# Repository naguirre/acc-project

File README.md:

# acc-project
Another Cubetto Clone project : this repository contains all assets (mechanical, sw and hardware) for ACC project

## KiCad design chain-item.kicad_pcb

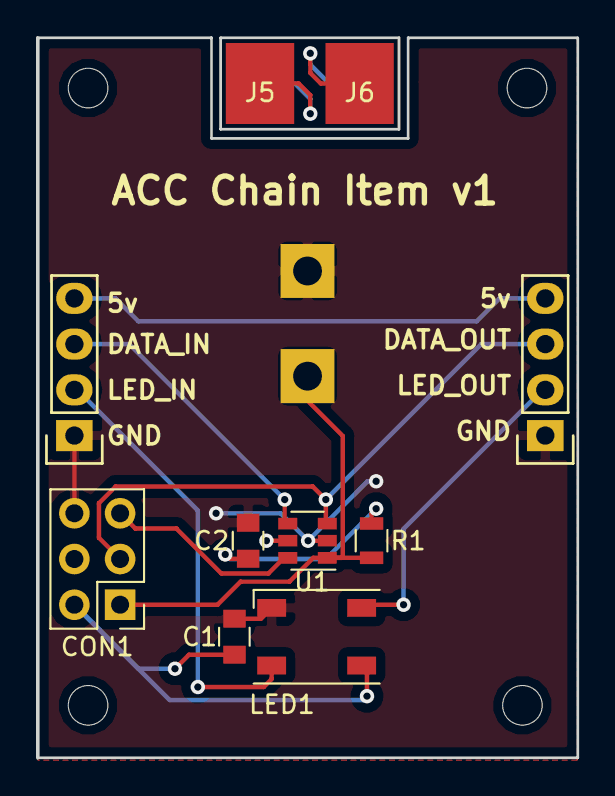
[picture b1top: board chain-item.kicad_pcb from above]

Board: 2 copper layers, 30.0 x 40.0 mm, 17 parts (1 on the bottom side), 11 nets.

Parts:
C1, C2: C_Small; C_0805
CON1: AVR-ISP-6; Pin_Header_Straight_2x03_Pitch2.54mm
J1, J4: Conn_01x04; Pin_Header_Straight_1x04
J2: R_PAD1; pogopin
J3: R_PAD2; pogopin
J5: R_PAD1; pad_resistor
J6: R_PAD2; pad_resistor
LED1: WS2812B; LED_WS2812B-PLCC4
MK11, MK12, MK13, MK14: Mounting_Hole; MountingHole_2.2mm_M2
R1, R2: R; R_0805
U1: ATTINY10-TS; SOT-23-6

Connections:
5V: J1.4, J4.4
+5V: C1.1, C2.1, CON1.2, LED1.1, R1.1, U1.5
DATA_IN: J1.3, U1.4
DATA_OUT: CON1.3, J4.3, U1.3
GND: C1.2, C2.2, CON1.6, J1.1, J3.1, J4.1, LED1.3, U1.2
LED_IN: J1.2, LED1.4
LED_OUT: J4.2, LED1.2
unnamed: CON1.1, J2.1, R1.2, U1.1
unnamed: CON1.5, U1.6
unnamed: J5.1, R2.1
unnamed: J6.1, R2.2

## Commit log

2018-05-01 Add description and version
2018-05-01 Add v1 sent to elecrow
2018-05-01 mv to hardware
2018-05-01 Mv others files
2018-05-01 Add few readme file
2018-05-03 First version of chain item code. Use https://www.avrfreaks.net/projects/software-uart-fifo?module=Freaks%20Academy&func=viewItem&item_id=1895&item_type=project
2018-05-03 More README
2018-05-05 Add hello world + wS2812 led code
2018-05-06 Add first import of robot software, create a dedicated component for odometry
2018-05-13 Add specific drivers for ESP32
2018-09-30 Add tcp server to control robot through socket
2018-10-01 add stuff
2018-10-01 udpate config
2018-10-01 Add test files
2020-04-04 Add robot_controller
2020-04-04 Bummp WIP
2020-04-04 gititnore++
2020-04-04 add config for main bozard
2020-04-04 Save main2 old backup
2020-04-04 Add file in hardware directory no clue what it is
2020-04-04 Update roboto_controller
2020-04-09 Add robot_controller flutter app
